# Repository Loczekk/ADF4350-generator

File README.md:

<!-- TABLE OF CONTENTS -->

<details>
  <summary>Table of Contents</summary>
  <ol>
    <li><a href="#about-the-project">About The Project</a></li>
    <li><a href="#introduction">Introduction</a></li>
    <li><a href="#final-parameters">Final parameters</a></li>
    <li><a href="#block-diagram">Block diagram</a></li>
    <li><a href="#pcb-design">PCB design</a></li>
    <li><a href="#cover-design">Cover design</a></li>
    <li><a href="#measurements">Measurements</a></li>
  </ol>
</details>

<!-- ABOUT THE PROJECT -->
## About The Project

My design of an RF generator based on the ADF4350, used as a heterodyne signal in my radiotelescope.

<p align="right">(<a href="#readme-top">back to top</a>)</p>

<!-- GETTING STARTED -->
## Introduction

The assumption of the project was to create a small and simple RF generator, with good parameters and high stability. At the very beginning, the generator design based on separate components was eliminated, i.e. separate VCO, PLL, dividers, multiplexers and final stages. Such a design can provide the best stability and noise parameters and be freely and easily modified, but it requires complex design and time-consuming tests. In this straightforward project, reliance is placed on the use of a Wideband Synthesizer with Integrated VCO, which will provide good parameters and in one "silicon" unit will have integrated basic components of the RF generator and the ability to program the output frequencies. I decided on the ADF4350 because of the parameters that were in line with the assumptions. What's more, the free samples I received from the manufacturer were an additional advantage.

<p align="right">(<a href="#readme-top">back to top</a>)</p>

## Final parameters

Dimensions: 

PCB: 51mm x 46mm,

Cover:  58mm x 53mm x 27mm

•	Power supply: +5V, >200mA

•	Output power: 9-15dBm

•	Frequency range: 550-4400MHz

•	4 programmable frequency values

•	SMA connectors

•	Frequency stability: +/- 350 Hz (depends on the frequency)

•	Phase noice: (-85) – (-105) dBc/Hz

•	Harmonics: -4dB (worst case)

<p align="right">(<a href="#readme-top">back to top</a>)</p>

## Block diagram

<p align="right">(<a href="#readme-top">back to top</a>)</p>

## PCB design

To maintain the intended dimensions and improve RF properties (thinner 50 Ohm paths), the PCB is 4-layer.
The design was based on a schematic diagram provided by the manufacturer in the catalog note. To ensure high stability, each voltage pin has its own stabilizer and copper plates. The mass is common, only under the quartz it is cut off. For easier assembly (soldering the ground pad), there is an enlarged hole in the PCB. The mounting holes were placed in convenient places due to the planned use of a 3D printed casing, designed for PCB. An exposed copper ring is used to mount the RF shielding.

<p align="right">(<a href="#readme-top">back to top</a>)</p>

## Cover design

The case was designed in Fusion360 using a PCB model generated in KiCad. 2 screws were used to screw the PCB to the lower part of the cover, another two were used to connect both parts of the case. There are also holes for 2 LEDs, a DC power and SMA connectors. To improve the appearance, the outer layers of the housing were printed using the Hilbert curve on an Ender 3 printer.

<p align="right">(<a href="#readme-top">back to top</a>)</p>

## Measurements

Measurements were made according to the connections shown in the diagram below. For this purpose, a Rohde&Schwarz FSV spectrum analyzer and a pendulum frequency counter, model CNT-104S, were used. The generator was powered by a laboratory power supply. All devices were turned on for at least 1 hour before the measurement to stabilize the temperature and achieve stable measurement conditions. The frequency stability measurement took 4 hours, after which the generator was switched to the input of the spectrum analyzer and after waiting 30 minutes, measurements of harmonics, signal power and phase noise were made. The procedure was repeated for 3 frequencies from different operating ranges of the ADF4350 synthesizer: 600MHz, 1380MHz and 2400MHz.

Measurement results for the 600MHz frequency:

•	Output frequency (exact): 600001200 Hz

•	Frequency stability: +/-150Hz

•	Power consumption: 0,79mW

•	Output power: 14,34 dBm

•	Phase noice (10kHz): -103,1dBc/Hz

•	Harmonics: 2nd: -9dB, 3rd: -20dB, 4th: -25dB

Measurement results for the 1380MHz frequency:

•	Output frequency (exact): 1380002470 Hz

•	Frequency stability: +/-300 Hz

•	Power consumption: 0,73 mW

•	Output power: 9,1 dBm

•	Phase noice (10 kHz): -90,25 dBc/Hz

•	Harmonics: 2nd: -16dB, 3rd: -4dB, 4th: -25dB

Measurement results for the 2400MHz frequency:

•	Output frequency (exact): 2400004910 Hz

•	Frequency stability: +/-350Hz

•	Power consumption: 0,72 mW 

•	Output power: 11,45 dBm

•	Phase noice (10kHz): -87,57 dBc/Hz

•	Harmonics: 2nd: -15dB, 3rd: out of range FSV

<p align="right">(<a href="#readme-top">back to top</a>)</p>

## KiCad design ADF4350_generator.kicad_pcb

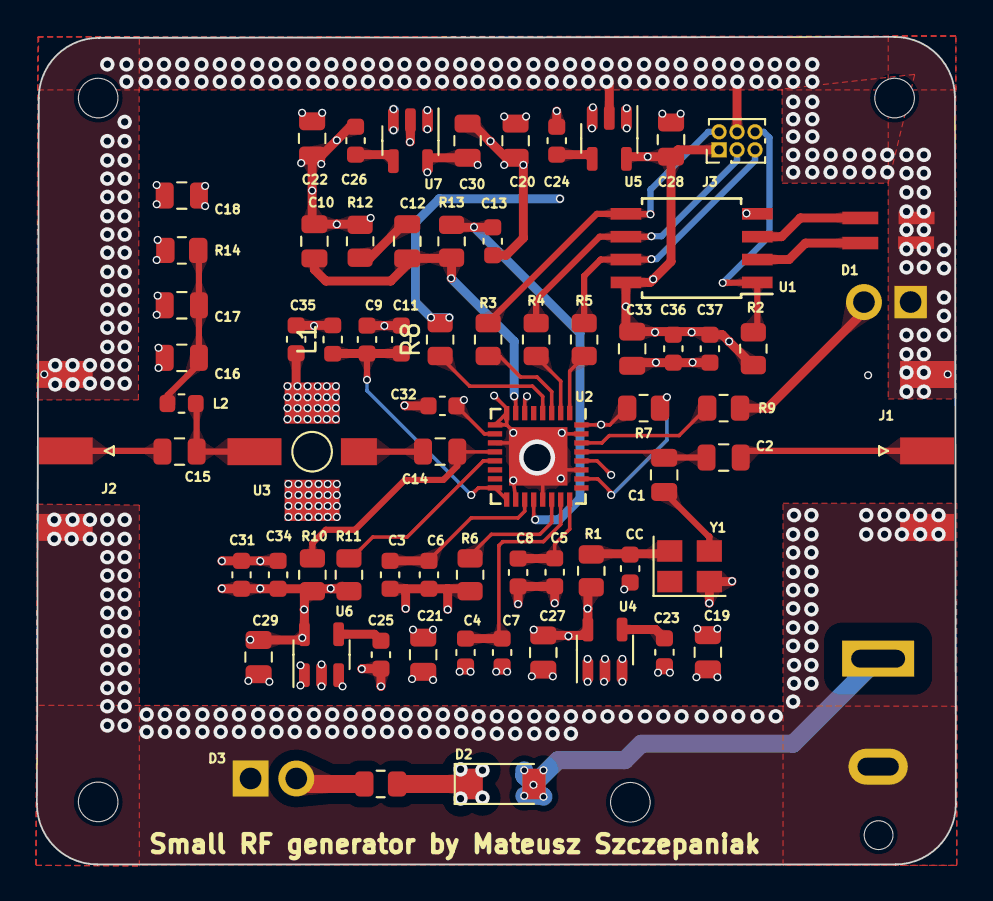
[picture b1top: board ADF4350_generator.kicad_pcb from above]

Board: 4 copper layers, 51.1 x 46.0 mm, 71 parts (1 on the bottom side), 43 nets.

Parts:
C1, C2, C17: 1n; C_0805_2012Metric
C3, C4, C5, C9, C34, C35, C37: 10p; C_0603_1608Metric
C6, C7, C8, C11, C31, C32, C36: 100n; C_0603_1608Metric
C10: 2n7; C_0805_2012Metric
C12: 47n; C_0805_2012Metric
C13: 1n2; C_0603_1608Metric
C14, C15: 22p; C_0805_2012Metric
C16: 100p; C_0805_2012Metric
C18, C27, C28, C29, C30: 4u7; C_0805_2012Metric
C19, C20, C21, C22, C33: 1u; C_0805_2012Metric
C23, C24, C25, C26: 10n; C_0603_1608Metric
CC: C_0603_1608Metric
D1, D3: LED; D_DO-15_P2.54mm_Vertical_AnodeUp
D2: LL4148; D_MiniMELF
J1: REF_IN; SMA_Amphenol_132289_EdgeMount
J2: RF_OUT; SMA_Amphenol_132289_EdgeMount
J3: Prog_conn; PinHeader_2x03_P1.00mm_Vertical
J4: Power_conn; BarrelJack_CUI_PJ-063AH_Horizontal
L1, L2: 47nH; L_0603_1608Metric
R1: 0; R_0805_2012Metric
R2, R7, R8: 10k; R_0805_2012Metric
R3, R4, R5, R9, R15: 2k; R_0805_2012Metric
R6: 4k7; R_0805_2012Metric
R10, R11: 51; R_0805_2012Metric
R12: 360; R_0805_2012Metric
R13: 680; R_0805_2012Metric
R14: 18; R_0805_2012Metric
SW1: SW_DIP_x02; PinHeader_2x02_P2.54mm_Vertical_SMD
U1: ATtiny13; SOIC-8W_5.3x5.3mm_P1.27mm
U2: ADF4350; LFCSP-32-1EP_5x5mm_P0.5mm_EP3.25x3.25mm
U3: type="X" model="OPAMP" lib=""; TO-50-4_ShortPad-NoHole_Housing
U4, U5, U6, U7: LP2985-2.8; SOT-23-5
Y1: 10MHz; Crystal_SMD_3225-4Pin_3.2x2.5mm

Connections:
5V: C18.1, C19.1, C20.1, C21.1, C22.1, D2.1 (K), R14.1, R15.1, U4.1 (VIN), U4.3 (ON/~OFF), U5.1 (VIN), U5.3 (ON/~OFF), U6.1 (VIN), U6.3 (ON/~OFF), U7.1 (VIN), U7.3 (ON/~OFF)
+5V: D2.2 (A), J4.2
/CLK: R5.2, U2.1 (CLK)
/DATA: R4.2, U2.2 (DATA)
/LE: R3.2, U2.3 (LE)
GND: C3.2, C4.2, C5.2, C6.2, C7.2, C8.2, C9.2, C10.1, C11.2, C13.1, C16.2, C17.2, C18.2, C19.2, C20.2, C21.2, C22.2, C23.2, C24.2, C25.2, C26.2, C27.2, C28.2, C29.2, C30.2, C31.2, C32.2, C33.2, C34.2, C35.2, C36.2, C37.2, CC.1, D1.1 (K), D3.1 (K), J1.2 (Ext), J2.2 (Ext), J3.3, J4.1, R6.1, R12.2, SW1.3, SW1.4, U1.4 (GND), U2.8 (CPGND), U2.9 (AGND), U2.11 (AGNDVCO), U2.18 (AGNDVCO), U2.21 (AGNDVCO), U2.27 (DGND), U2.31 (SDGND), U2.33 (EP), U3.1 (+), U3.4 (V+), U4.2 (GND), U5.2 (GND), U6.2 (GND), U7.2 (GND), Y1.2
unnamed: C1.2, Y1.3
unnamed: C9.1, C11.1, L1.1, U2.16 (VVCO), U2.17 (VVCO)
unnamed: C12.1, R12.1
unnamed: C15.1, L2.1, U3.3
unnamed: C16.1, C17.1, L2.2, R14.2
unnamed: D1.2 (A), R9.2
unnamed: D3.2 (A), R15.2
unnamed: C2.1, J1.1 (In)
unnamed: C15.2, J2.1 (In)
unnamed: J3.2, R3.1, U1.5 (PB0)
unnamed: J3.4, R4.1, U1.6 (PB1)
unnamed: J3.5, R5.1, U1.7 (PB2)
unnamed: J3.6, R2.2, U1.1 (~RESET/PB5)
unnamed: CC.2, R1.1, Y1.4 (1)
unnamed: SW1.1, U1.2 (PB3)
unnamed: SW1.2, U1.3 (PB4)
unnamed: R8.1, U2.4 (CE)
unnamed: C10.2, C12.2, R13.1, U2.7 (CPout)
unnamed: R9.1, U2.30 (MUXOUT)
unnamed: R7.1, U2.26 (PDB_RF)
unnamed: C1.1, C2.2, U2.29 (REFIN)
unnamed: C14.1, R10.1, U2.12 (RF_OUT_A+)
unnamed: R11.1, U2.13 (RF_OUT_A-)
unnamed: R6.2, U2.22 (RSET)
unnamed: C3.1, C6.1, U2.19 (TEMP)
unnamed: C4.1, C7.1, U2.23 (VCOM)
unnamed: C5.1, C8.1, U2.24 (VREF)
unnamed: C13.2, R13.2, U2.20 (VTUNE)
unnamed: C14.2, U3.2 (-)
unnamed: C23.1, U4.4 (BP)
unnamed: C24.1, U5.4 (BP)
unnamed: C25.1, U6.4 (BP)
unnamed: C26.1, U7.4 (BP)
Vdd1: C27.1, R1.2, U4.5 (VOUT)
Vdd2: C28.1, C33.1, C36.1, C37.1, J3.1, R2.1, R7.2, R8.2, U1.8 (VCC), U2.28 (DVDD), U2.32 (SDVDD), U5.5 (VOUT)
Vdd3: C29.1, C31.1, C34.1, R10.2, R11.2, U6.5 (VOUT)
Vdd4: C30.1, C32.1, C35.1, L1.2, U2.6 (Vp), U2.10 (AVDD), U7.5 (VOUT)

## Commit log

2024-07-29 KiCad files and stl of housing
2024-07-29 Create Gerbers
2024-07-29 add gerbers
